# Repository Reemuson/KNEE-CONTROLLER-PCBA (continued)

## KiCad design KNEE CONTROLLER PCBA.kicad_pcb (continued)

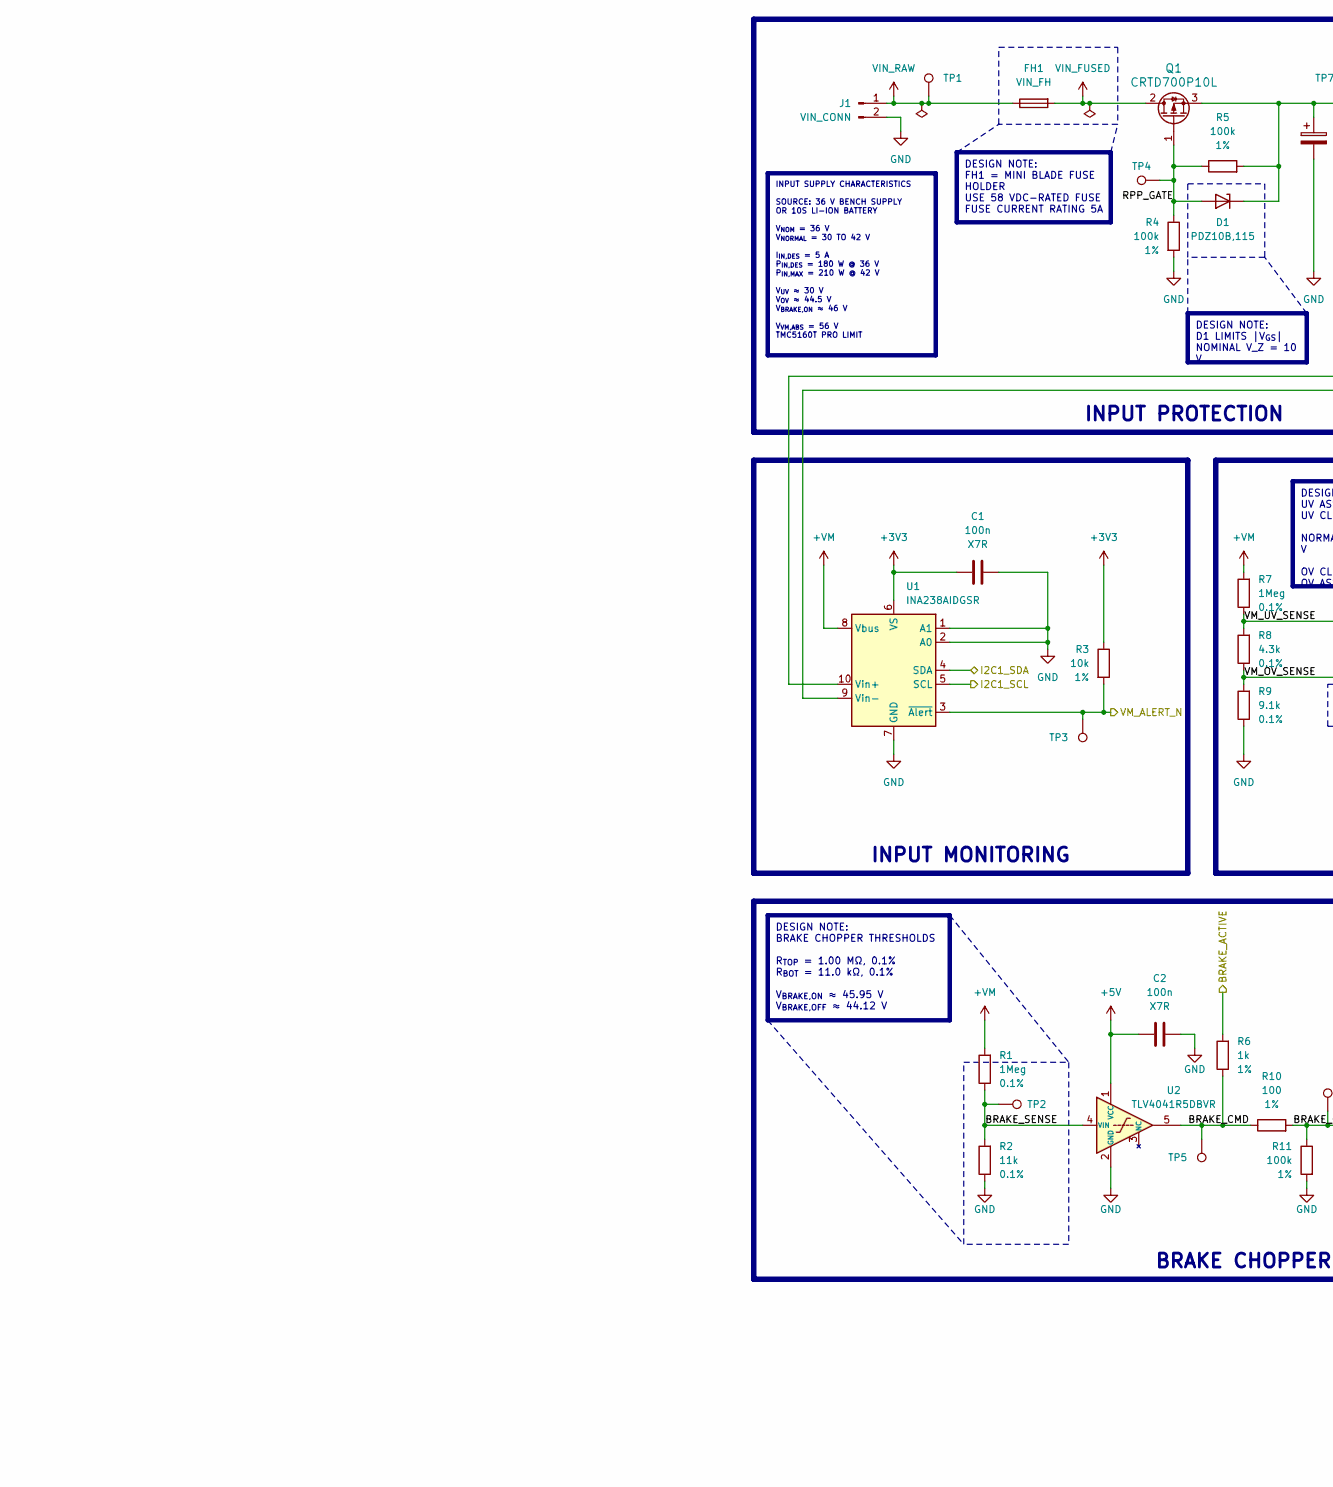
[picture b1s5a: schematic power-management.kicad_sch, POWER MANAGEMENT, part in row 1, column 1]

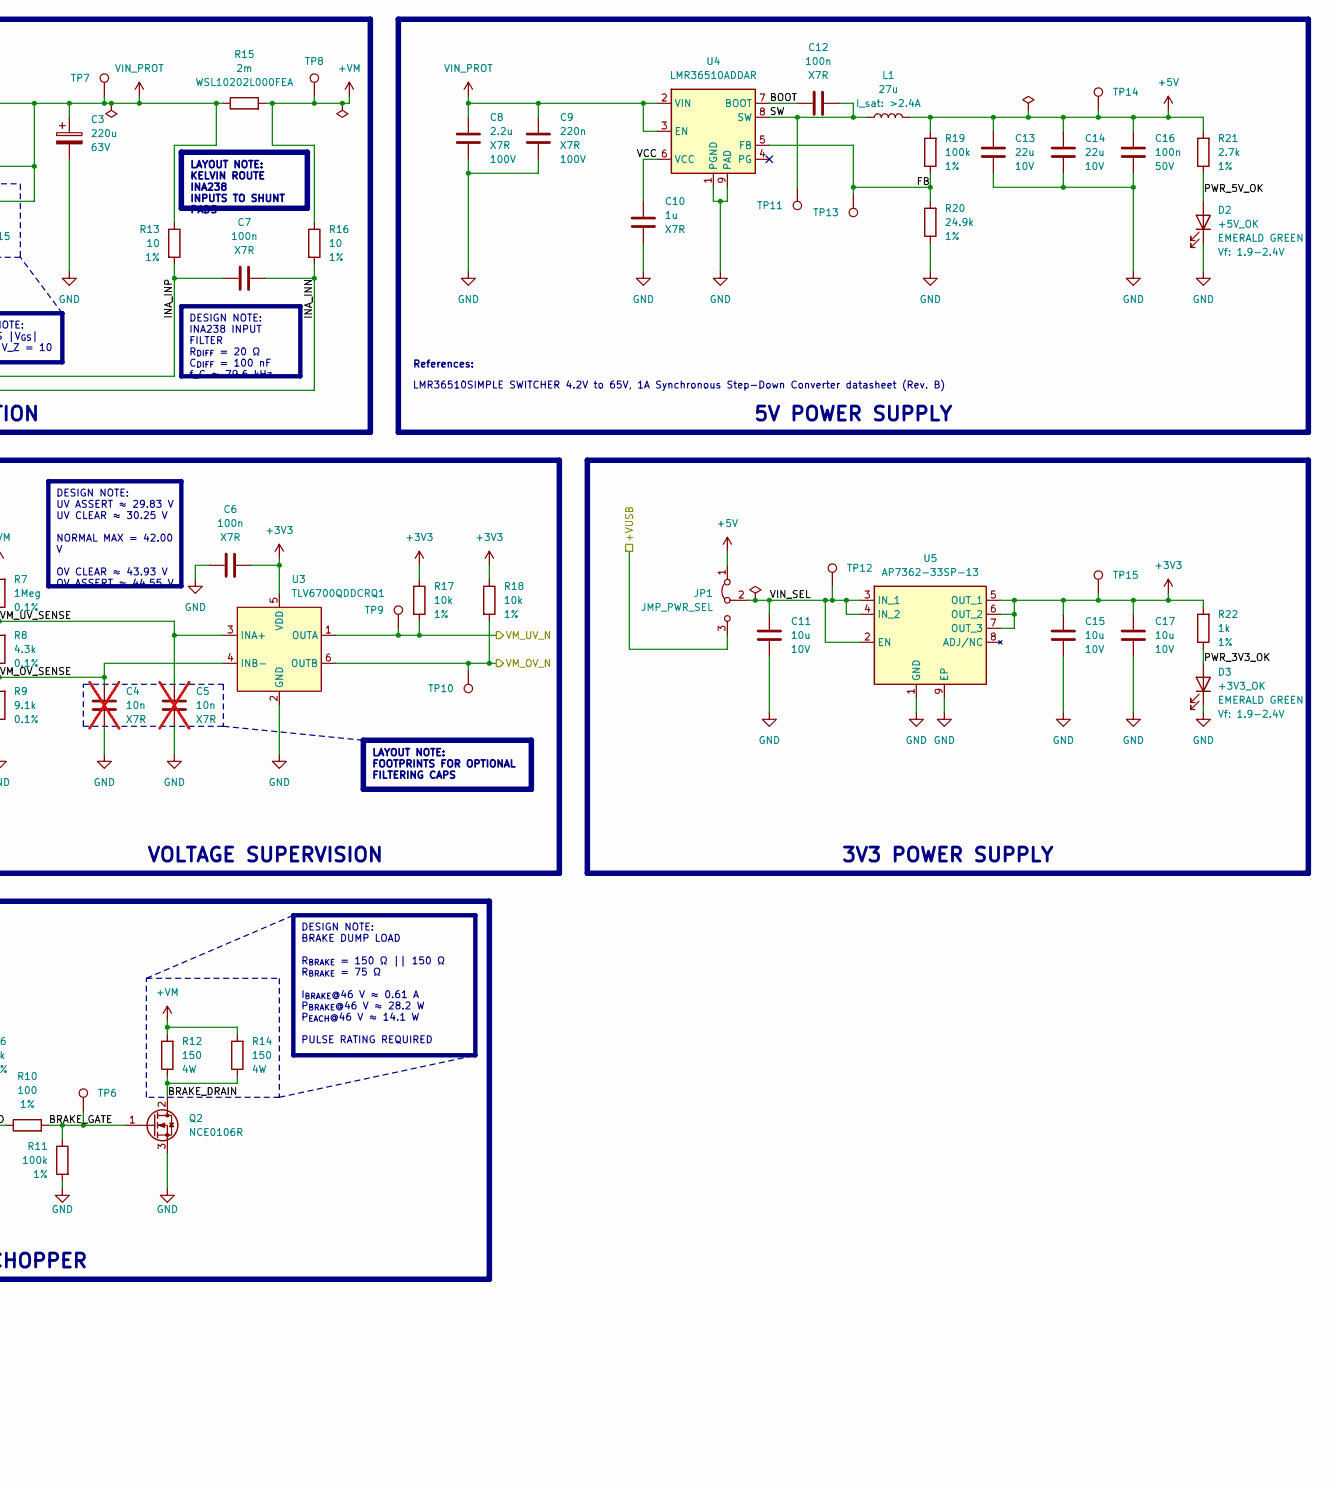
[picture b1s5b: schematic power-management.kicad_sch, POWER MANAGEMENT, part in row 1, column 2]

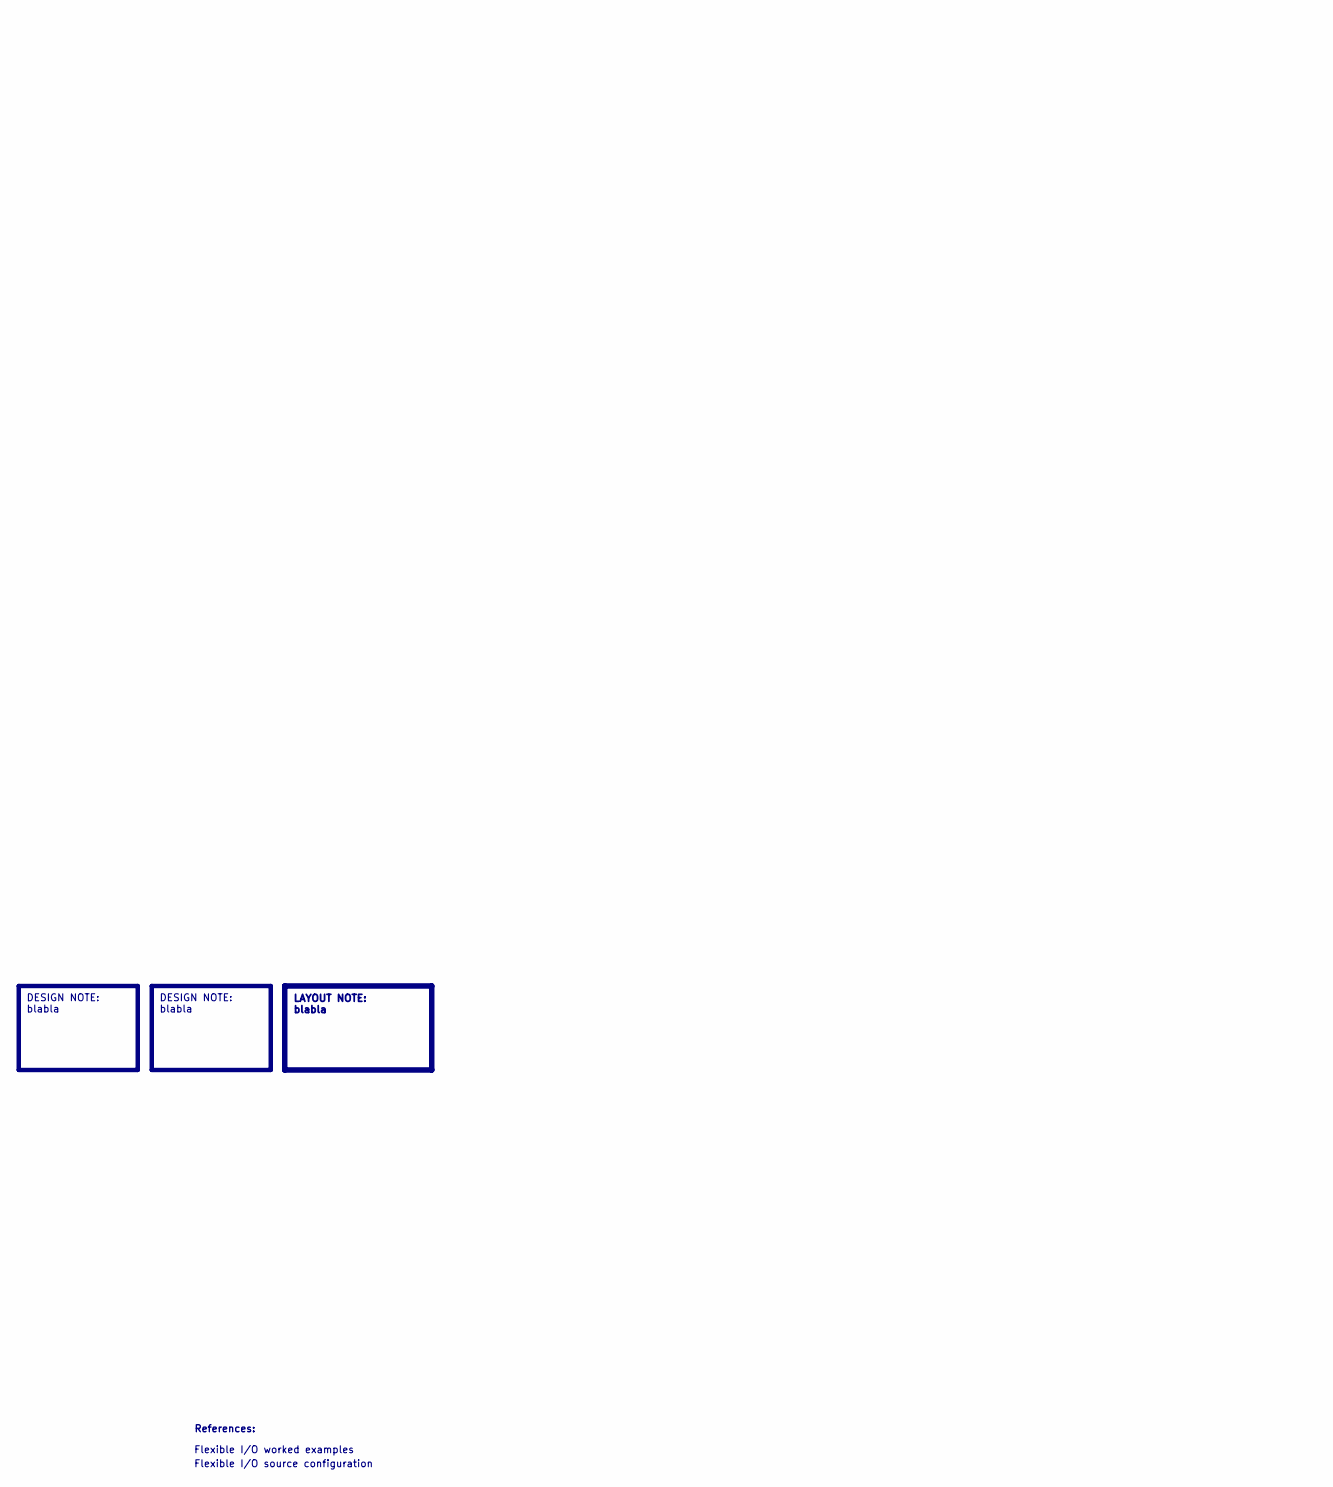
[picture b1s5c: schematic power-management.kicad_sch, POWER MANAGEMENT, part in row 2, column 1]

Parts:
C1, C2, C6, C7, C12, C16: 100n; C_0603_1608_DensityHigh; Voltage_Rating 50V; Tolerance 10%; MPN CC0603KRX7R9BB104
C3: 220u; CP_Radial_D10.0mm_P5.00mm; Voltage_Rating 63V; Tolerance 20%; MPN 63ZLJ220M10X16
C4, C5: 10n; C_0603_1608_DensityHigh; Voltage_Rating 50V; Tolerance 10%; MPN CC0603KRX7R9BB103; not fitted
C8: 2.2u; C_1206_3216_DensityHigh; Voltage_Rating 100V; Tolerance 10%; MPN CC1206KKX7R0BB225
C9: 220n; C_1206_3216_DensityHigh; Voltage_Rating 100V; Tolerance 10%; MPN CC1206KKX7R0BB224
C10: 1u; C_0805_2012_DensityHigh; Voltage_Rating 10V; Tolerance 10%; MPN CC0805MKX7R6BB105
C11, C15, C17: 10u; C_0805_2012_DensityHigh; Voltage_Rating 10V; Tolerance 10%; MPN CC0805KFX7R6BB106
C13, C14: 22u; C_1206_3216_DensityHigh; Voltage_Rating 10V; Tolerance 10%; MPN CC1206KKX7R6BB226
D1: PDZ10B,115; D_SOD-323; MPN PDZ10B,115
D2: +5V_OK; LED_0805_2012_DensityHigh; MPN LTST-C171KGKT
D3: +3V3_OK; LED_0805_2012_DensityHigh; MPN LTST-C171KGKT
FH1: VIN_FH; Fuseholder_Blade_Mini_Keystone_3568; MPN 3568
J1: VIN_CONN; Molex_KK-396_5273-02A_1x02_P3.96mm_Vertical; MPN 0436500215
JP1: JMP_PWR_SEL; PinHeader_1x03_P2.54mm_Vertical; MPN HM3212
L1: 27u; L_APV_ANR8040; Tolerance 20%; MPN ASPI-8040S-270M-T
Q1: CRTD700P10L; TO-252-2; Voltage_Rating 100V; MPN MCU055P10-TP
Q2: NCE0106R; SOT-223-3_TabPin2; Voltage_Rating 100V; MPN SL10N10A
R1, R7: 1Meg; R_0603_1608_DensityHigh; Tolerance 0.1%; Voltage_Rating 75V; MPN RT0603BRD071ML
R2: 11k; R_0603_1608_DensityHigh; Tolerance 0.1%; Voltage_Rating 75V; MPN RT0603BRD0711KL
R3, R17, R18: 10k; R_0603_1608_DensityHigh; Tolerance 1%; Voltage_Rating 75V; MPN RT0603FRE1010KL
R4, R5, R11, R19: 100k; R_0603_1608_DensityHigh; Tolerance 1%; Voltage_Rating 75V; MPN RT0603FRE07100KL
R6, R22: 1k; R_0603_1608_DensityHigh; Tolerance 1%; Voltage_Rating 75V; MPN RT0603FRE071KL
R8: 4.3k; R_0603_1608_DensityHigh; Tolerance 0.1%; Voltage_Rating 75V; MPN RT0603BRD074K32L
R9: 9.1k; R_0603_1608_DensityHigh; Tolerance 0.1%; Voltage_Rating 75V; MPN RT0603BRD079K1L
R10: 100; R_0603_1608_DensityHigh; Tolerance 1%; Voltage_Rating 75V; MPN RT0603FRE07100RL
R12, R14: 150; R_2512_6332Metric; Tolerance 5%; Voltage_Rating 250V; MPN RPCQ2512JT150R
R13, R16: 10; R_0603_1608_DensityHigh; Tolerance 1%; Voltage_Rating 75V; MPN RT0603FRE1310RL
R15: 2m; R_1020_2550Metric; Tolerance 1%; MPN WSL10202L000FEA
R20: 24.9k; R_0603_1608_DensityHigh; Tolerance 1%; Voltage_Rating 75V; MPN RT0603FRE0724K9L
R21: 2.7k; R_0603_1608_DensityHigh; Tolerance 1%; Voltage_Rating 75V; MPN RT0603FRE072K7L
TP1: VIN_RAW; TestPoint_Pad_D1.0mm
TP2: BRAKE_SENSE; TestPoint_Pad_D0.4mm
TP3: VM_ALERT_N; TestPoint_Pad_D0.4mm
TP4: RPP_GATE; TestPoint_Pad_D0.4mm
TP5: BRAKE_CMD; TestPoint_Pad_D0.4mm
TP6: BRAKE_GATE; TestPoint_Pad_D0.4mm
TP7: VIN_PROT; TestPoint_Pad_D1.0mm
TP8: +VM; TestPoint_Pad_D1.0mm
TP9: VM_UV_N; TestPoint_Pad_D0.4mm
TP10: VM_OV_N; TestPoint_Pad_D0.4mm
TP11: SW; TestPoint_Pad_D0.4mm
TP12: VIN_SEL; TestPoint_Pad_D0.4mm
TP13: FB; TestPoint_Pad_D0.4mm
TP14: +5V; TestPoint_Pad_D1.0mm
TP15: +3V3; TestPoint_Pad_D1.0mm
U1: INA238AIDGSR; VSSOP-10_3x3mm_P0.5mm; MPN INA238AIDGSR
U2: TLV4041R5DBVR; SOT-23-5; MPN TLV4041R5DBVR
U3: TLV6700QDDCRQ1; SOT-23-6; MPN TLV6700QDDCRQ1
U4: LMR36510ADDAR; Texas_HTSOP-8-1EP_3.9x4.9mm_P1.27mm_EP2.95x4.9mm_Mask2.4x3.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; Voltage_Rating 65V; MPN LMR36510ADDAR
U5: AP7362-33SP-13; SOIC-8-1EP_3.9x4.9mm_P1.27mm_EP2.6x3.5mm_ThermalVias; MPN AP7362-33SP-13

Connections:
+3V3: C1.2, C6.2, C15.2, C17.2, R3.1, R17.1, R18.1, R22.2, TP15.1, U1.6 (VS), U3.5 (VDD), U5.5 (OUT_1), U5.6 (OUT_2), U5.7 (OUT_3); also elsewhere on the board
+5V: C2.1, C13.2, C14.2, C16.1, JP1.1 (A), L1.2, R19.2, R21.2, TP14.1, U2.1 (VCC); also elsewhere on the board
+VM: R1.2, R7.2, R12.2, R14.2, R15.2, R16.1, TP8.1, U1.8 (Vbus); also elsewhere on the board
+VUSB: JP1.3 (B); also elsewhere on the board
/SYSTEM OVERVIEW/MICROCONTROLLER/BRAKE_ACTIVE: R6.2; also elsewhere on the board
/SYSTEM OVERVIEW/MICROCONTROLLER/I2C1_SCL: U1.5 (SCL); also elsewhere on the board
/SYSTEM OVERVIEW/MICROCONTROLLER/I2C1_SDA: U1.4 (SDA); also elsewhere on the board
/SYSTEM OVERVIEW/MICROCONTROLLER/VM_ALERT_N: R3.2, TP3.1, U1.3 (~Alert); also elsewhere on the board
/SYSTEM OVERVIEW/MICROCONTROLLER/VM_OV_N: R18.2, TP10.1, U3.6 (OUTB); also elsewhere on the board
/SYSTEM OVERVIEW/MICROCONTROLLER/VM_UV_N: R17.2, TP9.1, U3.1 (OUTA); also elsewhere on the board
/SYSTEM OVERVIEW/POWER MANAGEMENT/BOOT: C12.1, U4.7 (BOOT)
/SYSTEM OVERVIEW/POWER MANAGEMENT/BRAKE_CMD: R6.1, R10.1, TP5.1, U2.5
/SYSTEM OVERVIEW/POWER MANAGEMENT/BRAKE_DRAIN: Q2.2 (D), R12.1, R14.1
/SYSTEM OVERVIEW/POWER MANAGEMENT/BRAKE_GATE: Q2.1 (G), R10.2, R11.1, TP6.1
/SYSTEM OVERVIEW/POWER MANAGEMENT/BRAKE_SENSE: R1.1, R2.2, TP2.1, U2.4 (VIN)
/SYSTEM OVERVIEW/POWER MANAGEMENT/FB: R19.1, R20.2, TP13.1, U4.5 (FB)
/SYSTEM OVERVIEW/POWER MANAGEMENT/INA_INN: C7.2, R16.2, U1.9 (Vin-)
/SYSTEM OVERVIEW/POWER MANAGEMENT/INA_INP: C7.1, R13.2, U1.10 (Vin+)
/SYSTEM OVERVIEW/POWER MANAGEMENT/PWR_3V3_OK: D3.2 (A), R22.1
/SYSTEM OVERVIEW/POWER MANAGEMENT/PWR_5V_OK: D2.2 (A), R21.1
/SYSTEM OVERVIEW/POWER MANAGEMENT/RPP_GATE: D1.2 (A), Q1.1 (G), R4.1, R5.1, TP4.1
/SYSTEM OVERVIEW/POWER MANAGEMENT/SW: C12.2, L1.1, TP11.1, U4.8 (SW)
/SYSTEM OVERVIEW/POWER MANAGEMENT/VCC: C10.1, U4.6 (VCC)
/SYSTEM OVERVIEW/POWER MANAGEMENT/VIN_SEL: C11.2, JP1.2 (C), TP12.1, U5.2 (EN), U5.3 (IN_1), U5.4 (IN_2)
/SYSTEM OVERVIEW/POWER MANAGEMENT/VM_OV_SENSE: C4.2, R8.1, R9.2, U3.4 (INB-)
/SYSTEM OVERVIEW/POWER MANAGEMENT/VM_UV_SENSE: C5.2, R7.1, R8.2, U3.3 (INA+)
GND: C1.1, C2.2, C3.2, C4.1, C5.1, C6.1, C8.2, C9.2, C10.2, C11.1, C13.1, C14.1, C15.1, C16.2, C17.1, D2.1 (K), D3.1 (K), J1.2, Q2.3 (S), R2.1, R4.2, R9.1, R11.2, R20.1, U1.1 (A1), U1.2 (A0), U1.7 (GND), U2.2 (GND), U3.2 (GND), U4.1 (PGND), U4.9 (PAD), U5.1 (GND), U5.9 (EP); also elsewhere on the board
VIN_FUSED: FH1.2, Q1.2 (D)
VIN_PROT: C3.1, C8.1, C9.1, D1.1 (K), Q1.3 (S), R5.2, R13.1, R15.1, TP7.1, U4.2 (VIN), U4.3 (EN)
VIN_RAW: FH1.1, J1.1, TP1.1

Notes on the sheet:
References:
Flexible I/O worked examples
Flexible I/O source configuration
LMR36510SIMPLE SWITCHER 4.2V to 65V, 1A Synchronous Step-Down Converter datasheet (Rev. B)
DESIGN NOTE: UV ASSERT ≈ 29.83 V UV CLEAR ≈ 30.25 V NORMAL MAX = 42.00 V OV CLEAR ≈ 43.93 V OV ASSERT ≈ 44.55 V
DESIGN NOTE: BRAKE CHOPPER THRESHOLDS R_{TOP} = 1.00 MΩ, 0.1% R_{BOT} = 11.0 kΩ, 0.1% V_{BRAKE,ON} ≈ 45.95 V V_{BRAKE,OFF} ≈ 44.12 V
DESIGN NOTE: FH1 = MINI BLADE FUSE HOLDER USE 58 VDC-RATED FUSE FUSE CURRENT RATING 5A
VOLTAGE SUPERVISION
DESIGN NOTE: blabla
LAYOUT NOTE: blabla
DESIGN NOTE: BRAKE DUMP LOAD R_{BRAKE} = 150 Ω || 150 Ω R_{BRAKE} = 75 Ω I_{BRAKE}@46 V ≈ 0.61 A P_{BRAKE}@46 V ≈ 28.2 W P_{EACH}@46 V ≈ 14.1 W PULSE RATING REQUIRED
3V3 POWER SUPPLY
INPUT SUPPLY CHARACTERISTICS SOURCE: 36 V BENCH SUPPLY OR 10S LI-ION BATTERY V_{NOM} = 36 V V_{NORMAL} = 30 TO 42 V I_{IN,DES} = 5 A P_{IN,DES} = 180 W @ 36 V P_{IN,MAX} = 210 W @ 42 V V_{UV} ≈ 30 V V_{OV} ≈ 44.5 V V_{BRAKE,ON} ≈ 46 V V_{VM,ABS} = 56 V TMC5160T PRO LIMIT
5V POWER SUPPLY
BRAKE CHOPPER
LAYOUT NOTE: FOOTPRINTS FOR OPTIONAL FILTERING CAPS
INPUT PROTECTION
DESIGN NOTE: INA238 INPUT FILTER R_{DIFF} = 20 Ω C_{DIFF} = 100 nF f_C ≈ 79.6 kHz
DESIGN NOTE: D1 LIMITS |V_{GS}| NOMINAL V_Z = 10 V
INPUT MONITORING
LAYOUT NOTE: KELVIN ROUTE INA238 INPUTS TO SHUNT PADS

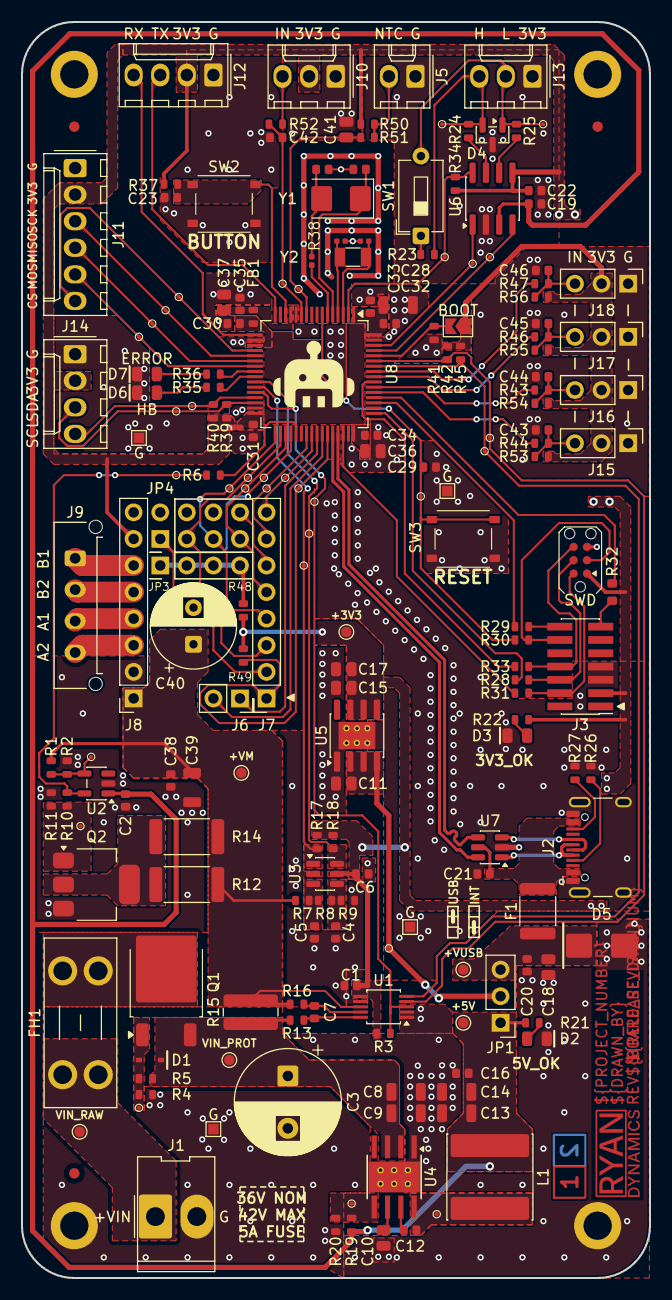
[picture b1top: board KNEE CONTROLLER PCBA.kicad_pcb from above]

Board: 2 copper layers, 60.0 x 120.0 mm, 203 parts (0 on the bottom side), 105 nets.
